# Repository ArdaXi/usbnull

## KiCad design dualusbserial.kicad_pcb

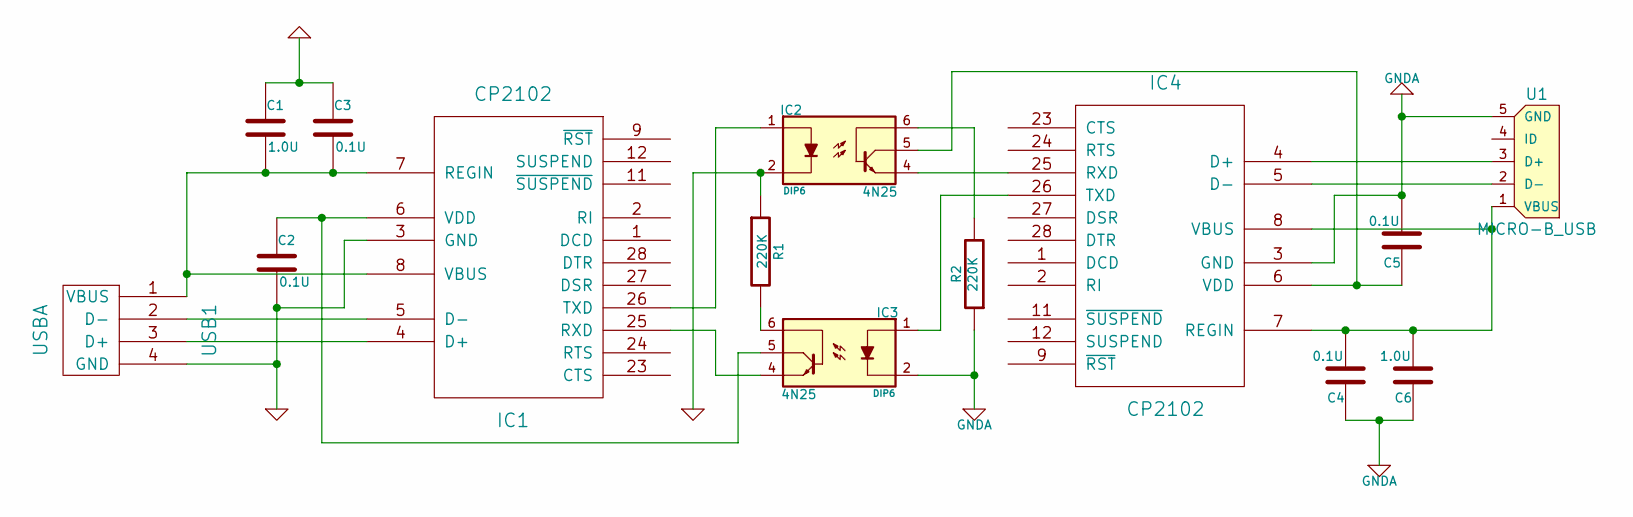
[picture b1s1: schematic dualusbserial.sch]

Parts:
C1, C6: 1.0U
C2, C3, C4, C5: 0.1U
IC1, IC4: CP2102
IC2, IC3: 4N25; DIP6
R1, R2: 220K
U1: MICRO-B_USB
USB1: USBA

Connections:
GND: C1.1, C2.2, C3.1, IC1.3 (GND), IC2.2, R1.1, USB1.4 (GND)
GNDA: C4.1, C5.2, C6.1, IC3.2, IC4.3 (GND), R2.1, U1.5 (GND)
unnamed: IC4.5 (D-), U1.2 (D-)
unnamed: IC4.4 (D+), U1.3 (D+)
unnamed: IC2.4, IC4.25 (RXD)
unnamed: IC3.1, IC4.26 (TXD)
unnamed: C5.1, IC2.5, IC4.6 (VDD)
unnamed: IC2.6, R2.2
unnamed: C4.2, C6.2, IC4.7 (REGIN), IC4.8 (VBUS), U1.1 (VBUS)
unnamed: C1.2, C3.2, IC1.7 (REGIN), IC1.8 (VBUS), USB1.1 (VBUS)
unnamed: IC1.26 (TXD), IC2.1
unnamed: IC1.25 (RXD), IC3.4
unnamed: IC3.6, R1.2
unnamed: IC1.4 (D+), USB1.3 (D+)
unnamed: IC1.5 (D-), USB1.2 (D-)
unnamed: C2.1, IC1.6 (VDD), IC3.5

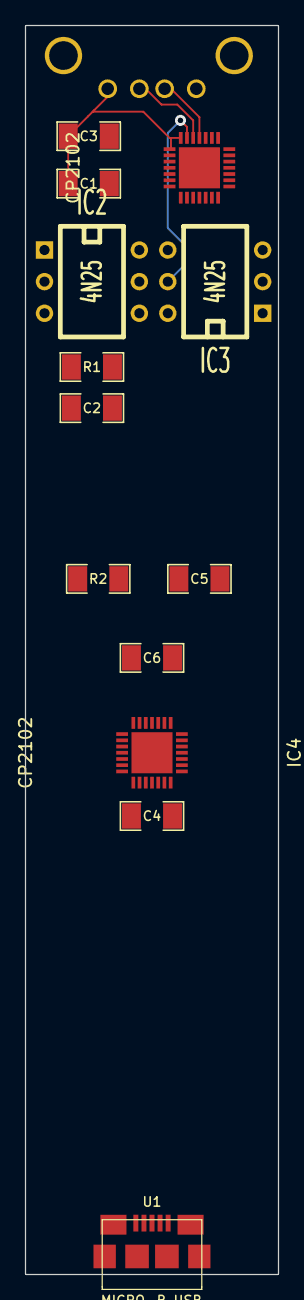
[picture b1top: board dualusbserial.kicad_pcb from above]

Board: 2 copper layers, 20.3 x 100.3 mm, 14 parts (1 on the bottom side), 16 nets.

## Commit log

2014-05-06 Added open-project lib
2014-05-07 Initial PCB
